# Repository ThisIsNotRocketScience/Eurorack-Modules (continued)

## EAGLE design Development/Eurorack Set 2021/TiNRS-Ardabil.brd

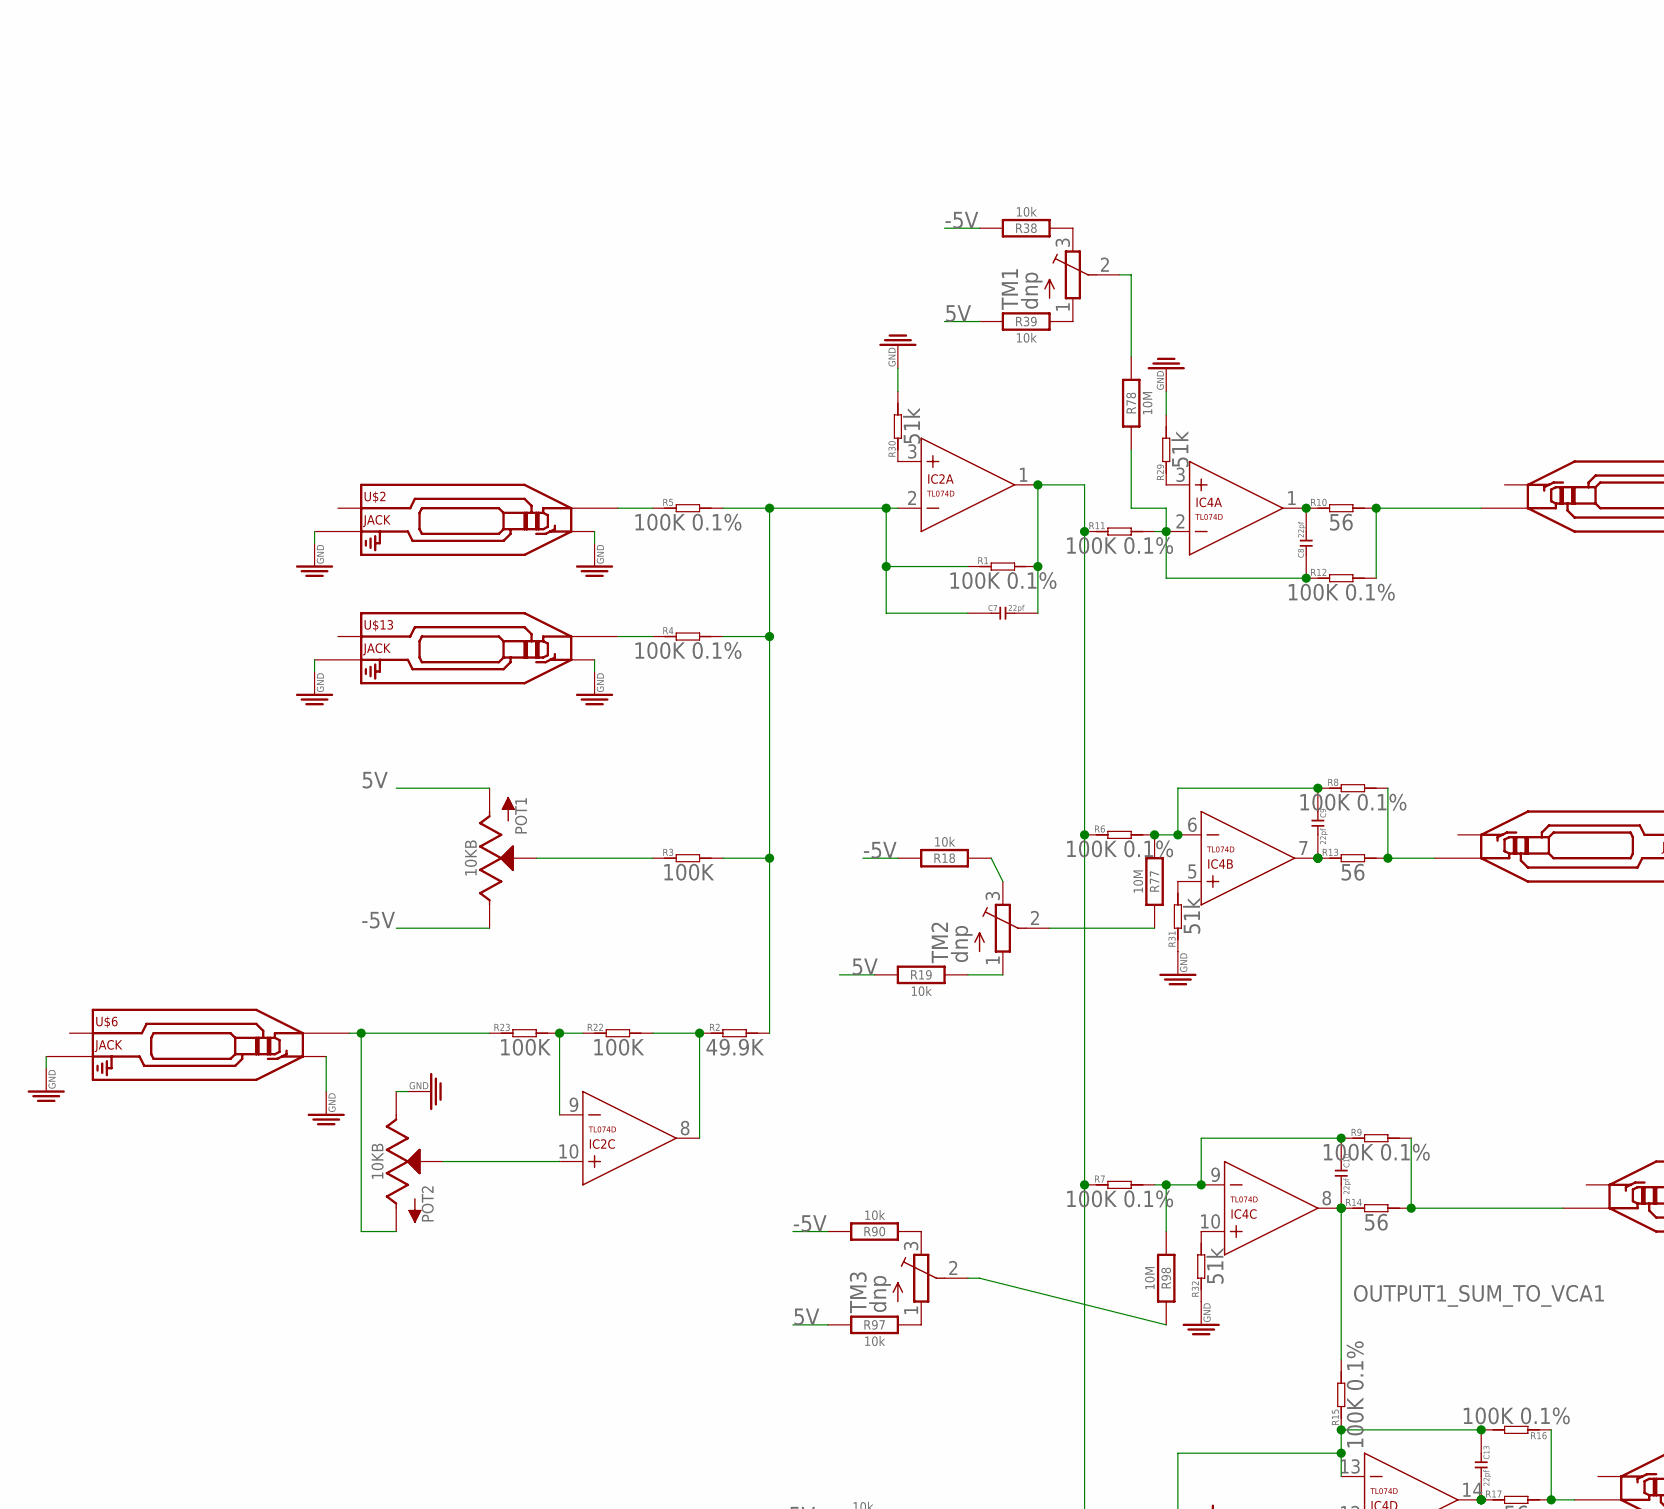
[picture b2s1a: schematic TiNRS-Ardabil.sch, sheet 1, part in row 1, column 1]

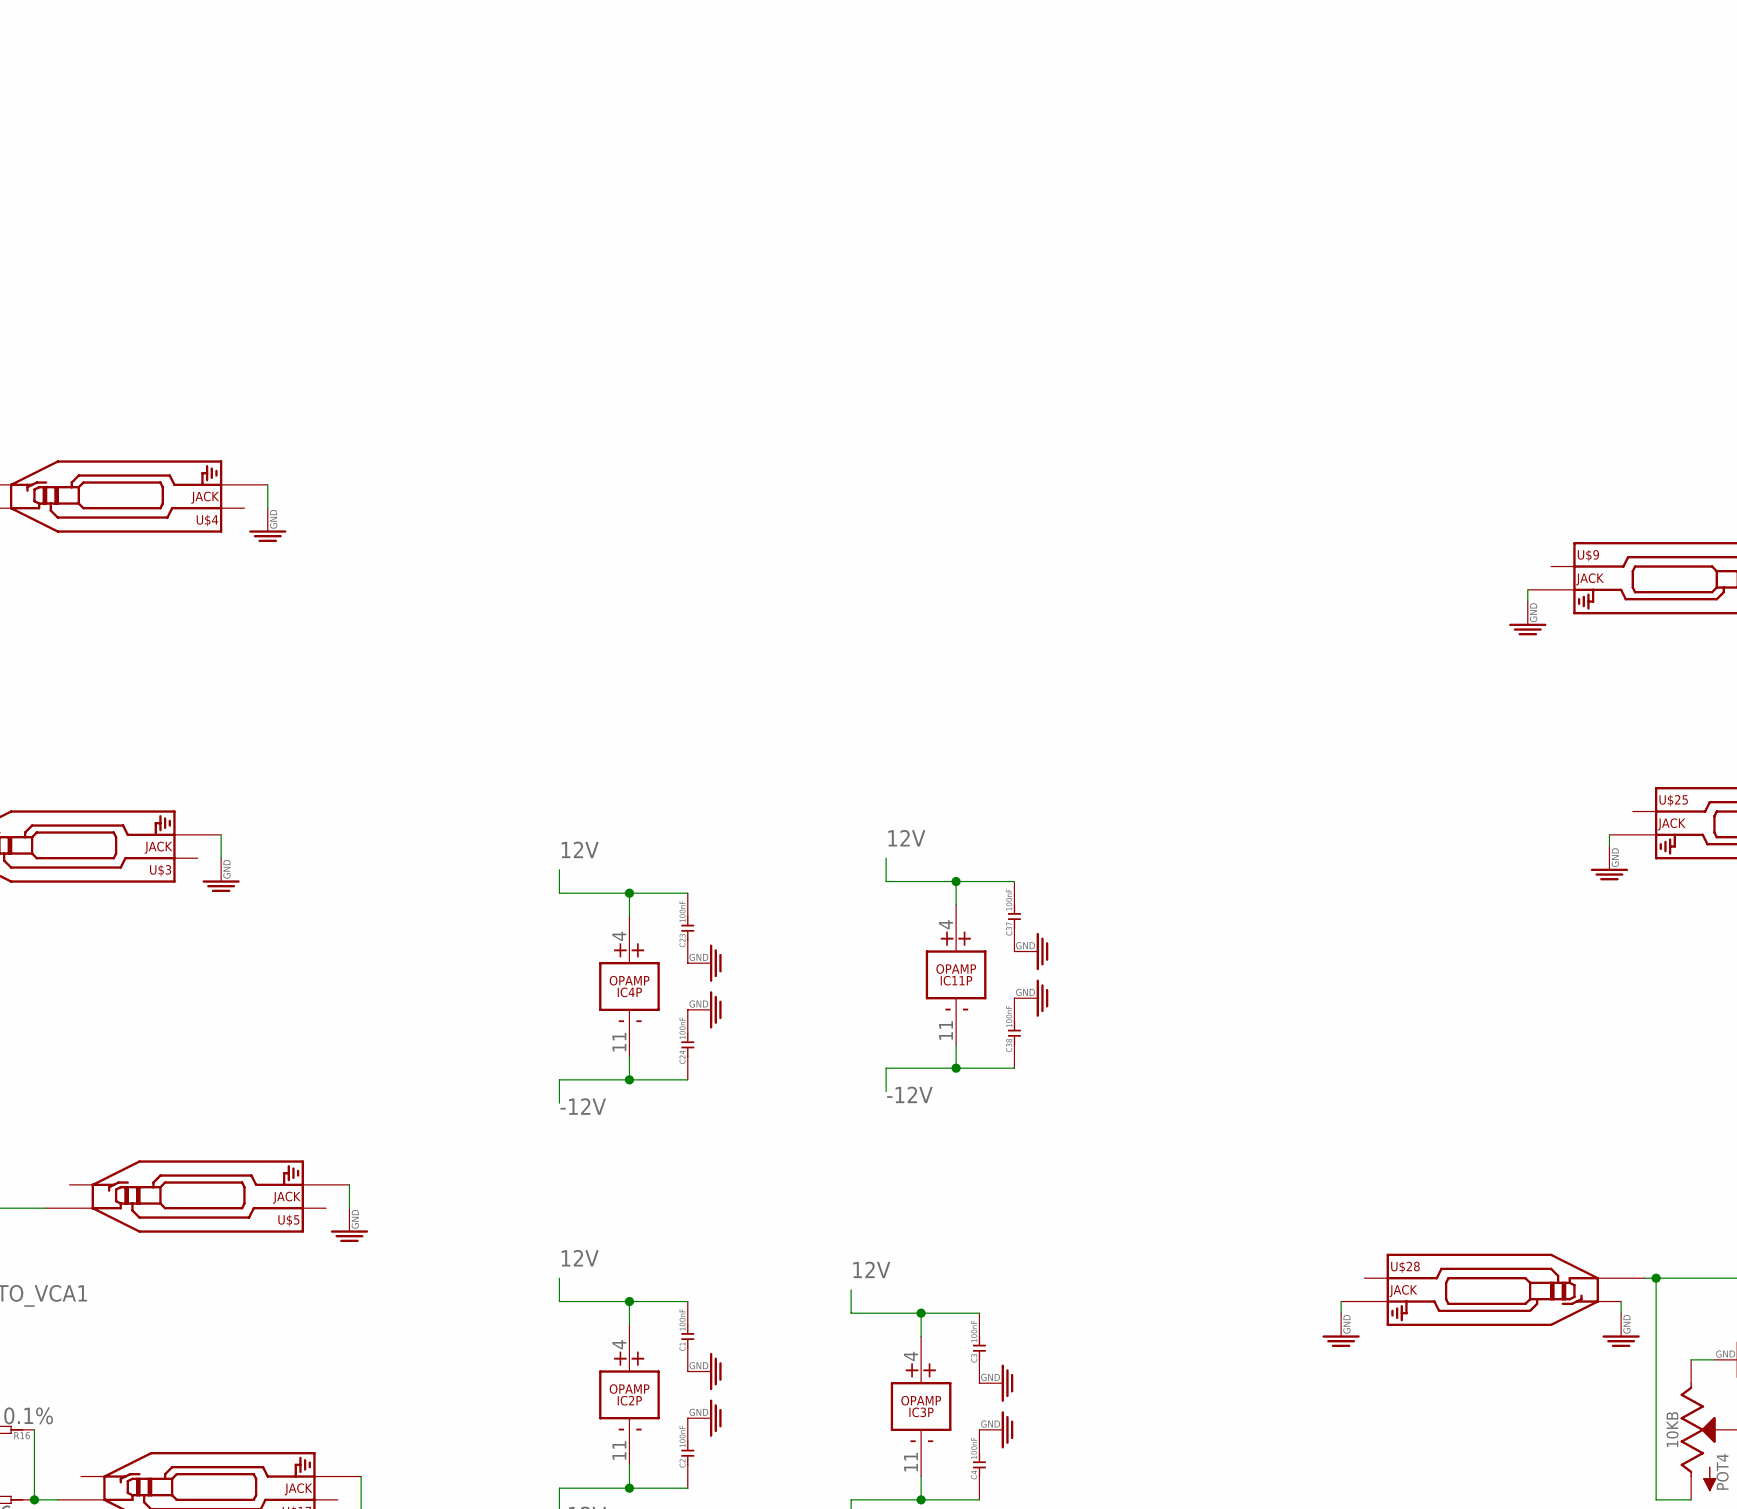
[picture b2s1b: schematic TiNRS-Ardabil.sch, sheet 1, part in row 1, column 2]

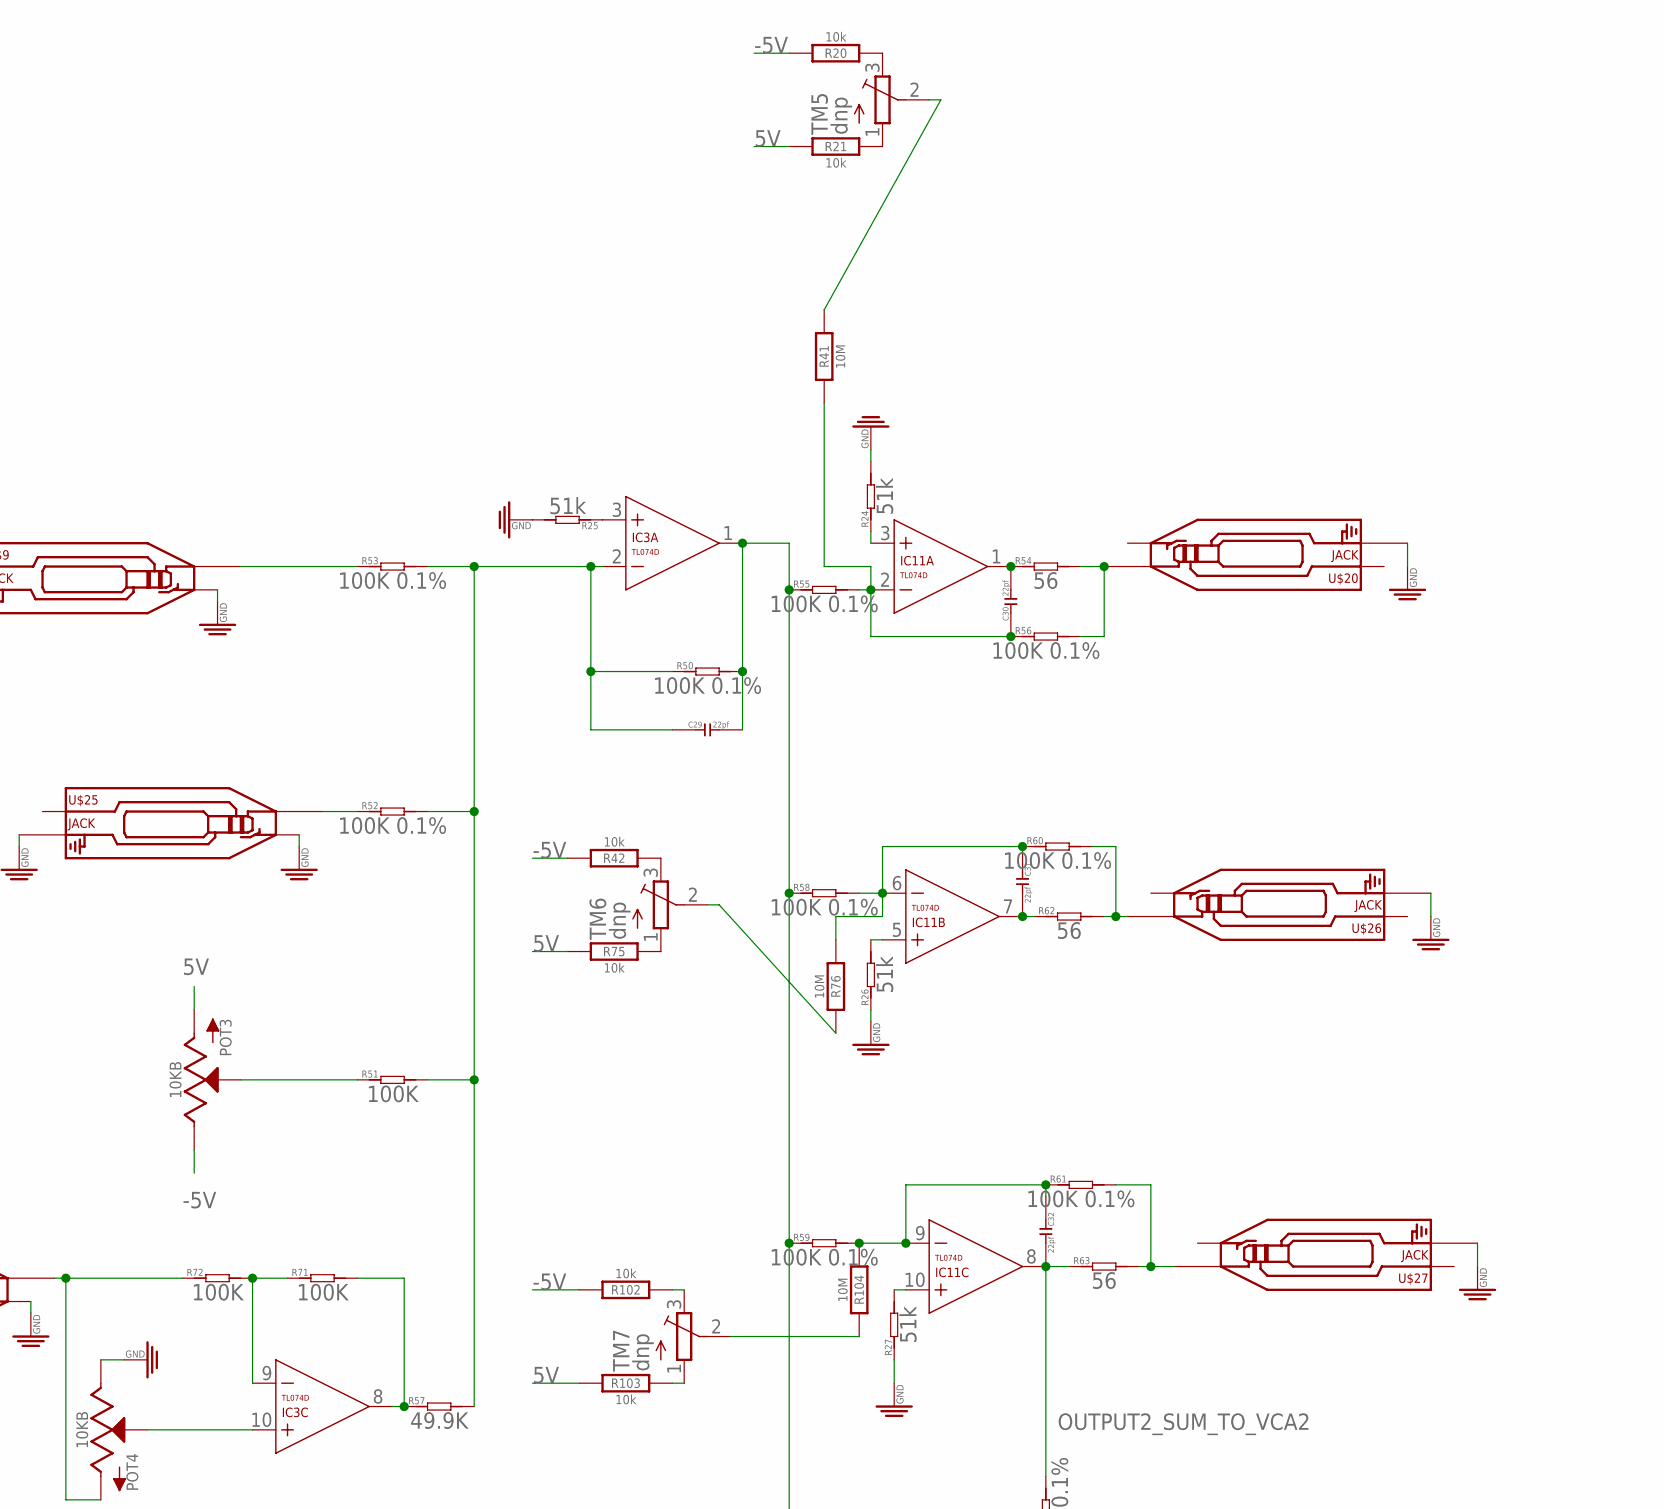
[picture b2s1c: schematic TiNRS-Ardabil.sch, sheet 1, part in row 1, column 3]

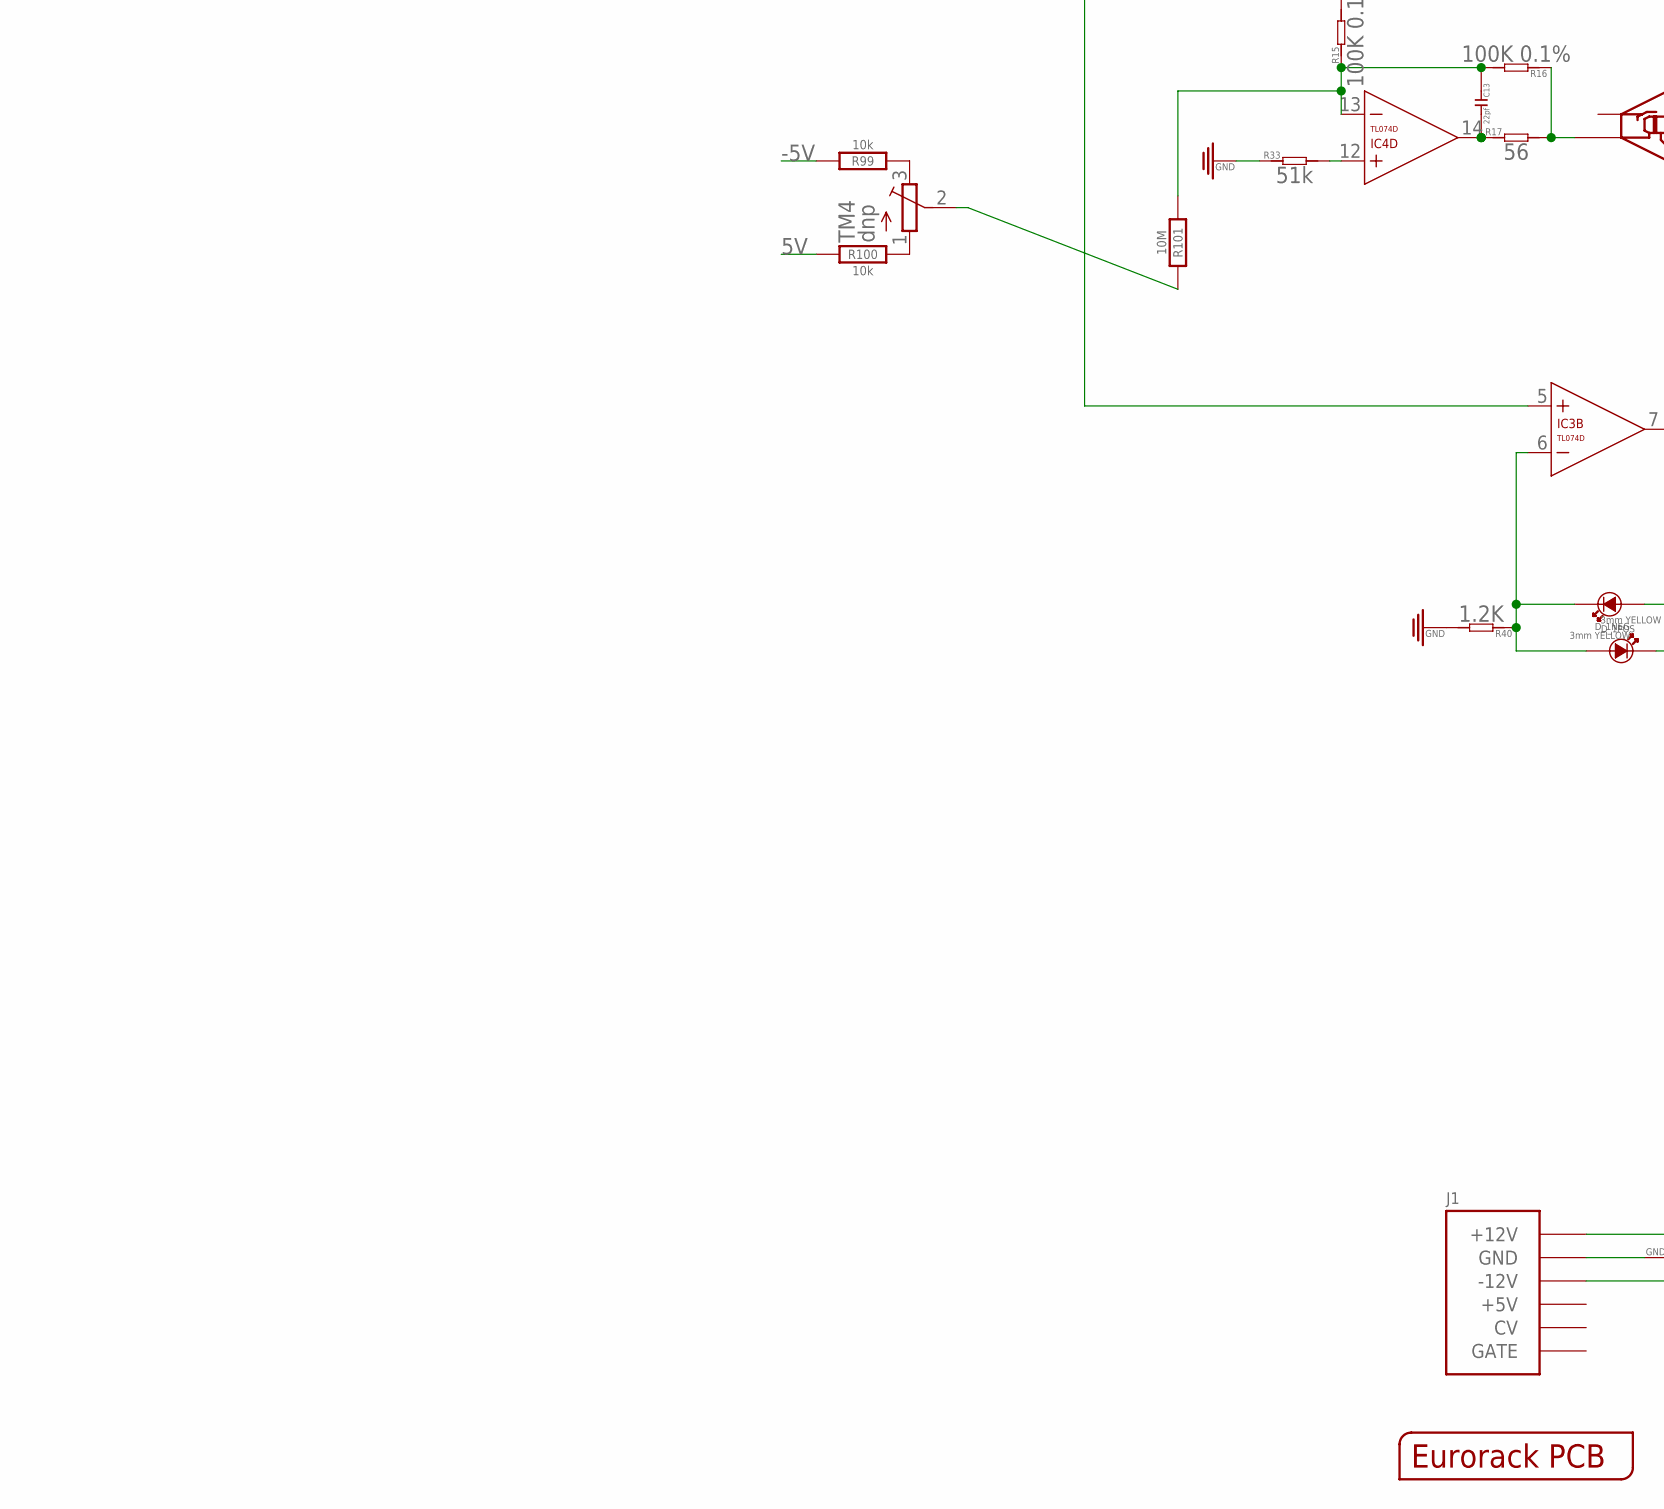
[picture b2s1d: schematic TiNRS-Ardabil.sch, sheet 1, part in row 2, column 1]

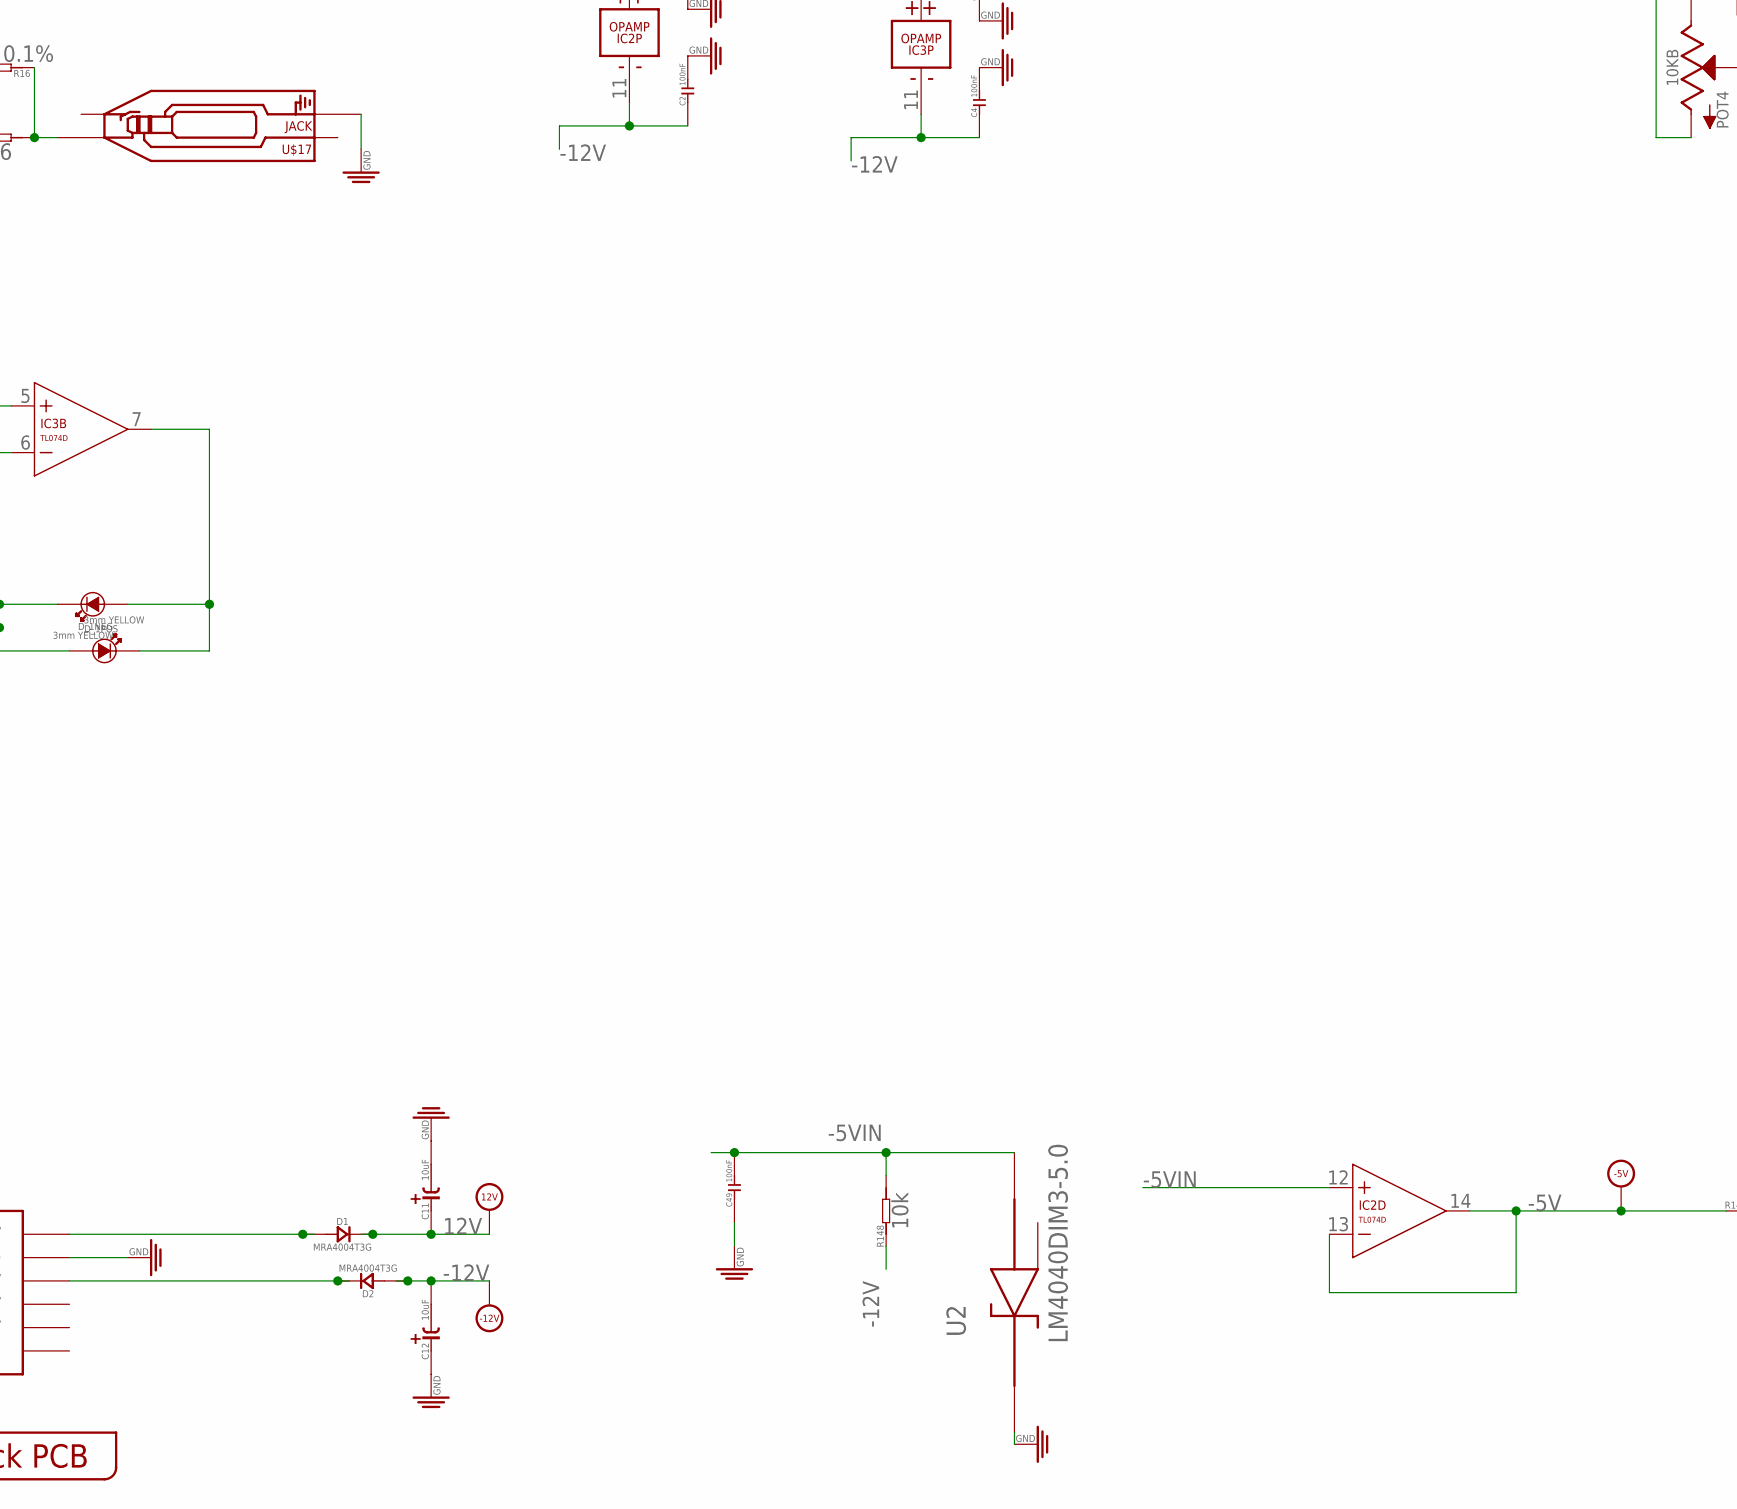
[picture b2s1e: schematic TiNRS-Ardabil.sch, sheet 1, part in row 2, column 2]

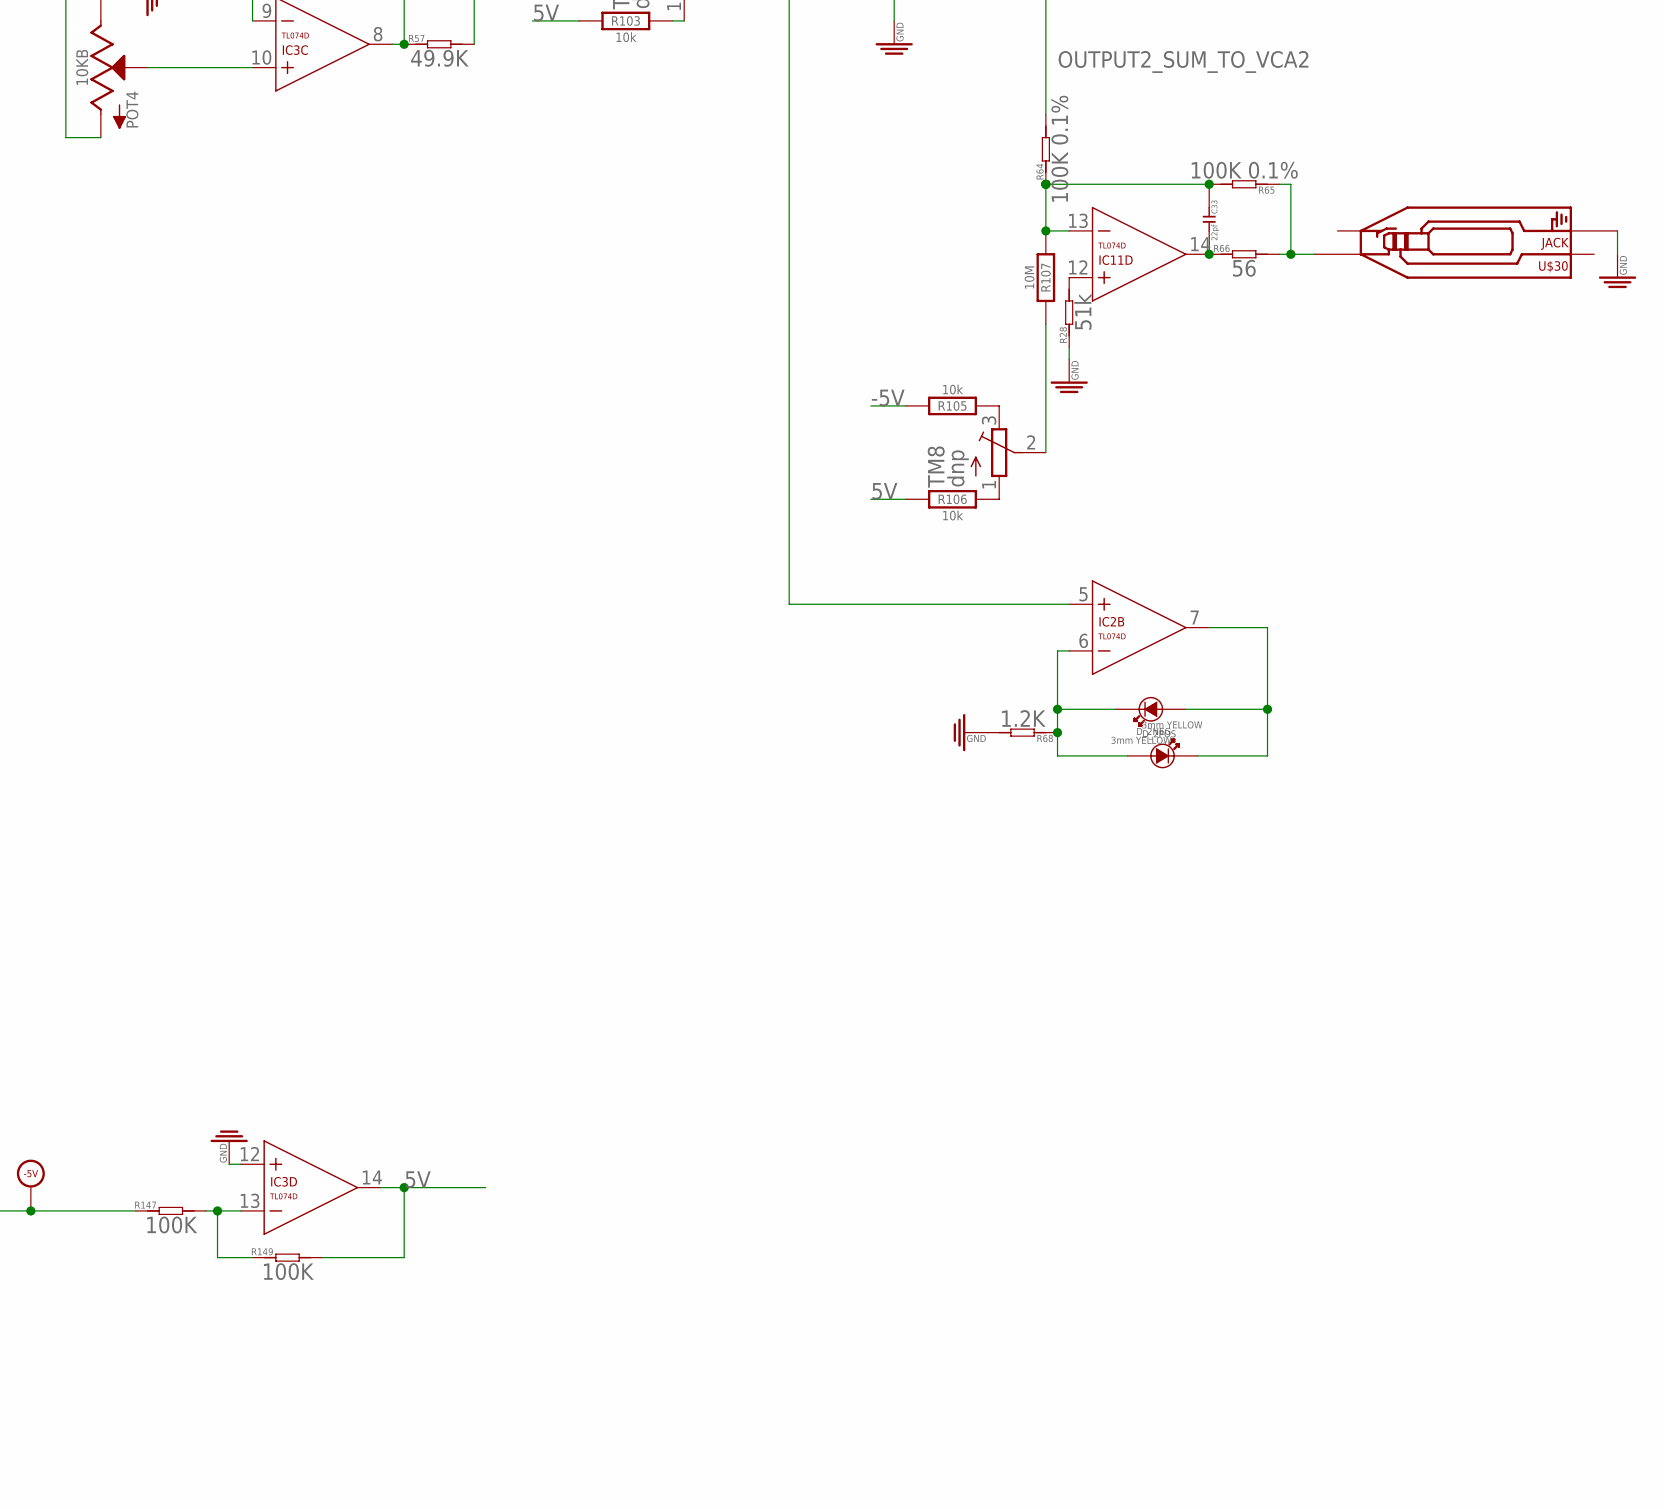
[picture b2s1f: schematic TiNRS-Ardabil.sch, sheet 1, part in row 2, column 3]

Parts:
C1, C2, C3, C4, C23, C24, C37, C38: 100nF; C0603
C7, C8, C9, C10, C13, C29, C30, C31, C32, C33: 22pf; C0603
C11, C12: 10uF; CASE-A_3216
C49: 100nF; C0603; MPN 06035C104KAT2A
D1, D2: MRA4004T3G; DO-214AC; MPN US1G-E3/5AT
D_1NEG, D_1POS, D_2NEG, D_2POS: 3mm YELLOW; 3MMLED
IC2, IC3, IC4, IC11: TL074D; SO14
J1: POWER_SHROUDED_NOTEXT; POWER_16_SHROUDED_NOTEXT
POT1, POT2, POT3, POT4: 10KB; ALPS_POT_SQUAREHOLES
R1, R4, R5, R6, R7, R8, R9, R11, R12, R15, R16, R50, R52, R53, R55, R56, R58, R59, R60, R61, R64, R65: 100K 0.1%; R0603
R2, R57: 49.9K; R0603
R3, R22, R23, R51, R71, R72, R147, R149: 100K; R0603
R10, R13, R14, R17, R54, R62, R63, R66: 56; R0603
R18, R19, R20, R21, R38, R39, R42, R75, R90, R97, R99, R100, R102, R103, R105, R106: 10k; R0402
R24, R25, R26, R27, R28, R29, R30, R31, R32, R33: 51k; R0603
R40, R68: 1.2K; R0603
R41, R76, R77, R78, R98, R101, R104, R107: 10M; R0402
R148: 10k; R0603
TM1, TM2, TM3, TM4, TM5, TM6, TM7, TM8: dnp; TC33X
U2: LM4040DIM3-5.0; SOT95P237X112-3N
U$1: EURORACK_PCB12HP; EURORACK12HPPCB
U$2, U$3, U$4, U$5, U$6, U$9, U$13, U$17, U$20, U$25, U$26, U$27, U$28, U$30: JACK; 3.5MM-JACK-SWITCH-13MM-NOHOLES-TESTPAD

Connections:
5V: IC3.14 (OUT), POT1.P$3 (A), POT3.P$3 (A), R19.2, R21.2, R39.2, R75.2, R97.2, R100.2, R103.2, R106.2, R149.2
12V: C1.2, C3.2, C11.+ (1), C23.2, C37.2, D1.2 (-), IC2.4 (V+), IC3.4 (V+), IC4.4 (V+), IC11.4 (V+); also elsewhere on the board
-5V: IC2.13 (-IN), IC2.14 (OUT), POT1.P$1 (E), POT3.P$1 (E), R18.1, R20.1, R38.1, R42.1, R90.1, R99.1, R102.1, R105.1, R147.1; also elsewhere on the board
-5VIN: C49.2, IC2.12 (+IN), R148.2, U2.2 (ANODE)
-5V_TO_5V: IC3.13 (-IN), R147.2, R149.1
-12V: C2.1, C4.1, C12.- (2), C24.1, C38.1, D2.1 (+), IC2.11 (V-), IC3.11 (V-), IC4.11 (V-), IC11.11 (V-), R148.1; also elsewhere on the board
GND: C1.1, C2.2, C3.1, C4.2, C11.- (2), C12.+ (1), C23.1, C24.2, C37.1, C38.2, C49.1, IC3.12 (+IN), J1.3 (GND), J1.4 (GND), J1.5 (GND), J1.6 (GND), J1.7 (GND), J1.8 (GND), POT2.P$1 (E), POT4.P$1 (E), R24.2, R25.2, R26.1, R27.1, R28.1, R29.2, R30.2, R31.1, R32.1, R33.1, R40.2, R68.2, U2.1 (CATHODE), U$2.RING_B@1 (RING), U$2.RING_T@3 (RING), U$2.SWITCH_B@1 (SWITCH), U$2.SWITCH_T@3 (SWITCH), U$3.RING_B@1 (RING), U$3.RING_T@3 (RING), U$4.RING_B@1 (RING), U$4.RING_T@3 (RING), U$5.RING_B@1 (RING), U$5.RING_T@3 (RING), U$6.RING_B@1 (RING), U$6.RING_T@3 (RING), U$6.SWITCH_B@1 (SWITCH), U$6.SWITCH_T@3 (SWITCH), U$9.RING_B@1 (RING), U$9.RING_T@3 (RING), U$9.SWITCH_B@1 (SWITCH), U$9.SWITCH_T@3 (SWITCH), U$13.RING_B@1 (RING), U$13.RING_T@3 (RING), U$13.SWITCH_B@1 (SWITCH), U$13.SWITCH_T@3 (SWITCH), U$17.RING_B@1 (RING), U$17.RING_T@3 (RING), U$20.RING_B@1 (RING), U$20.RING_T@3 (RING), U$25.RING_B@1 (RING), U$25.RING_T@3 (RING), U$25.SWITCH_B@1 (SWITCH), U$25.SWITCH_T@3 (SWITCH), U$26.RING_B@1 (RING), U$26.RING_T@3 (RING), U$27.RING_B@1 (RING), U$27.RING_T@3 (RING), U$28.RING_B@1 (RING), U$28.RING_T@3 (RING), U$28.SWITCH_B@1 (SWITCH), U$28.SWITCH_T@3 (SWITCH), U$30.RING_B@1 (RING), U$30.RING_T@3 (RING); also elsewhere on the board
unnamed: IC2.10 (+IN), POT2.P$2 (S)
unnamed: C8.2, IC4.1 (OUT), R10.1
unnamed: IC2.8 (OUT), R2.1, R22.2
unnamed: POT2.P$3 (A), R23.1, U$6.TIP_B@1 (TIP), U$6.TIP_T@3 (TIP)
unnamed: C9.1, IC4.6 (-IN), R6.2, R8.1, R77.2
unnamed: POT1.P$2 (S), R3.1
unnamed: C7.2, IC2.1 (OUT), IC3.5 (+IN), R1.2, R6.1, R7.1, R11.1
unnamed: R38.2, TM1.3 (E)
unnamed: C10.1, IC4.9 (-IN), R7.2, R9.1, R98.2
unnamed: IC2.9 (-IN), R22.1, R23.2
unnamed: C9.2, IC4.7 (OUT), R13.1
unnamed: R4.1, U$13.TIP_B@1 (TIP), U$13.TIP_T@3 (TIP)
unnamed: R60.2, R62.2, U$26.TIP_B@1 (TIP), U$26.TIP_T@3 (TIP)
unnamed: C7.1, IC2.2 (-IN), R1.1, R2.2, R3.2, R4.2, R5.2
unnamed: R8.2, R13.2, U$3.TIP_B@1 (TIP), U$3.TIP_T@3 (TIP)
unnamed: R9.2, R14.2, U$5.TIP_B@1 (TIP), U$5.TIP_T@3 (TIP)
unnamed: C13.1, IC4.13 (-IN), R15.1, R16.2, R101.2
unnamed: C13.2, IC4.14 (OUT), R17.1
unnamed: R16.1, R17.2, U$17.TIP_B@1 (TIP), U$17.TIP_T@3 (TIP)
unnamed: R5.1, U$2.TIP_B@1 (TIP), U$2.TIP_T@3 (TIP)
unnamed: R20.2, TM5.3 (E)
unnamed: R10.2, R12.2, U$4.TIP_B@1 (TIP), U$4.TIP_T@3 (TIP)
unnamed: IC11.12 (+IN), R28.2
unnamed: IC11.10 (+IN), R27.2
unnamed: IC11.3 (+IN), R24.1
unnamed: IC3.3 (+IN), R25.1
unnamed: D1.1 (+), J1.9 (+12V), J1.10 (+12V)
unnamed: IC11.5 (+IN), R26.2
unnamed: R65.1, R66.2, U$30.TIP_B@1 (TIP), U$30.TIP_T@3 (TIP)
unnamed: R21.1, TM5.1 (A)
unnamed: R39.1, TM1.1 (A)
unnamed: IC2.3 (+IN), R30.1
unnamed: R18.2, TM2.3 (E)
unnamed: IC4.10 (+IN), R32.2
unnamed: IC4.12 (+IN), R33.2
unnamed: D_1NEG.-, D_1POS.+, IC3.6 (-IN), R40.1
unnamed: D_1NEG.+, D_1POS.-, IC3.7 (OUT)
unnamed: IC4.5 (+IN), R31.2
unnamed: C8.1, IC4.2 (-IN), R11.2, R12.1, R78.2
unnamed: IC4.3 (+IN), R29.1
unnamed: R78.1, TM1.2 (S)
unnamed: R19.1, TM2.1 (A)
unnamed: R77.1, TM2.2 (S)
unnamed: R90.2, TM3.3 (E)
unnamed: C30.2, IC11.1 (OUT), R54.1
unnamed: POT3.P$2 (S), R51.1
unnamed: R97.1, TM3.1 (A)
unnamed: R98.1, TM3.2 (S)
unnamed: R99.2, TM4.3 (E)
unnamed: R100.1, TM4.1 (A)
unnamed: R101.1, TM4.2 (S)
unnamed: R41.1, TM5.2 (S)
unnamed: R42.2, TM6.3 (E)
unnamed: R52.1, U$25.TIP_B@1 (TIP), U$25.TIP_T@3 (TIP)
unnamed: D2.2 (-), J1.1 (-12V), J1.2 (-12V)
unnamed: C29.1, IC3.2 (-IN), R50.1, R51.2, R52.2, R53.2, R57.2
unnamed: R54.2, R56.2, U$20.TIP_B@1 (TIP), U$20.TIP_T@3 (TIP)
unnamed: C29.2, IC2.5 (+IN), IC3.1 (OUT), R50.2, R55.1, R58.1, R59.1
unnamed: C30.1, IC11.2 (-IN), R41.2, R55.2, R56.1
unnamed: R53.1, U$9.TIP_B@1 (TIP), U$9.TIP_T@3 (TIP)
unnamed: POT4.P$3 (A), R72.1, U$28.TIP_B@1 (TIP), U$28.TIP_T@3 (TIP)
unnamed: C31.1, IC11.6 (-IN), R58.2, R60.1, R76.2
unnamed: C32.1, IC11.9 (-IN), R59.2, R61.1, R104.2
unnamed: C31.2, IC11.7 (OUT), R62.1
unnamed: R75.1, TM6.1 (A)
unnamed: R61.2, R63.2, U$27.TIP_B@1 (TIP), U$27.TIP_T@3 (TIP)
unnamed: C33.1, IC11.13 (-IN), R64.1, R65.2, R107.2
unnamed: C33.2, IC11.14 (OUT), R66.1
unnamed: R76.1, TM6.2 (S)
unnamed: D_2NEG.-, D_2POS.+, IC2.6 (-IN), R68.1
unnamed: D_2NEG.+, D_2POS.-, IC2.7 (OUT)
unnamed: R102.2, TM7.3 (E)
unnamed: R103.1, TM7.1 (A)
unnamed: IC3.10 (+IN), POT4.P$2 (S)
unnamed: IC3.8 (OUT), R57.1, R71.2
unnamed: IC3.9 (-IN), R71.1, R72.2
unnamed: R104.1, TM7.2 (S)
unnamed: R105.2, TM8.3 (E)
unnamed: R106.1, TM8.1 (A)
unnamed: R107.1, TM8.2 (S)
OUTPUT1_SUM_TO_VCA1: C10.2, IC4.8 (OUT), R14.1, R15.2; also elsewhere on the board
OUTPUT2_SUM_TO_VCA2: C32.2, IC11.8 (OUT), R63.1, R64.2; also elsewhere on the board
